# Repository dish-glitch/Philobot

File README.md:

# Philo — Autonomous Person-Following Robot

**A 4-wheeled ground robot that locks onto a person using real-time YOLOv8 pose detection and follows them across a room. Raise your hand and it stops. Lower it and it follows again.**

---

## Schematic Preview

---

## PCB Preview

---

## Chassis Preview

*Coming soon — Fusion 360 render in progress*

---

## What It Does

A Raspberry Pi 5 runs YOLOv8 pose estimation on a live camera feed, detects the nearest person in frame, and continuously streams direction and speed commands to an ESP32 over UART. The ESP32 runs closed-loop PID speed control on four DC motors via dual H-bridge drivers. Three ultrasonic sensors on the front of the chassis act as an independent safety layer — if an obstacle is detected under 25cm, the ESP32 overrides the Pi command and stops regardless of what the vision stack says.

**Gesture control:** YOLOv8 tracks 17 body keypoints per person. When either wrist keypoint rises above the shoulder keypoint in frame coordinates, the Pi switches to STOP mode and holds it for 5 consecutive frames before acting — this debounces the detection and prevents flickering. Lowering the hand for 5 consecutive frames resumes following. Stop gesture confirmed working in testing.

**Sign language recognition:** The camera detects ASL hand signs in real time using MediaPipe hand landmarks and a trained classifier. Recognized letters are sent over UART to the ESP32 and displayed live on the onboard OLED (bench-tested on the Arduino stand-in; the ESP32 `ASL` handler is implemented and awaiting PCB bring-up). Initial testing on Pi 5 shows strong results for most letters — broader testing across different hands, lighting, and environments is still in progress.

**Obstacle avoidance:** Three HC-SR04 ultrasonic sensors (front-left at -30 degrees, front-center, front-right at +30 degrees) feed into a priority layer in ESP32 firmware. The Pi handles direction. The ESP32 handles not hitting things. These are separate concerns and intentionally kept that way.

---

## How It Works

```
+--------------------------------------------------+
|              Raspberry Pi 5                      |
|                                                  |
|  Camera -> YOLOv8n-pose -> keypoint extraction   |
|               |                                  |
|      Person bounding box offset                  |
|      Wrist vs. shoulder Y position               |
|               |                                  |
|      State machine (FOLLOWING / WAITING)         |
|               |                                  |
|      Serial command -> UART TX                   |
+---------------+----------------------------------+
                |  115200 baud UART
                |  Format: CMD <left> <right> <flags>  (-255..255)
                v
+--------------------------------------------------+
|              ESP32-WROOM-32                      |
|                                                  |
|  UART RX -> parse command                        |
|               |                                  |
|  Ultrasonic check (priority override)            |
|               |                                  |
|  PID speed control per motor side                |
|  PWM via LEDC peripheral at 20kHz               |
|               |                                  |
|  TB6612FNG x2 -> 4 DC motors with encoders      |
+--------------------------------------------------+
```

**Latency budget (targets):**

| Stage | Target |
|---|---|
| Camera capture | ~5ms |
| YOLOv8n-pose inference (imgsz=320) | ~70ms |
| Serial transmission | ~1ms |
| ESP32 motor response | ~5ms |
| **Total loop** | **~80ms (~12 Hz)** |

12 Hz is sufficient for following a walking person. A running person would expose the lag — but that is not the use case.

**Why UART and not I2C or SPI:** UART is asynchronous and trivially debuggable with a serial monitor. I2C requires the ESP32 to act as master which complicates the Pi-side code. SPI is faster than needed. UART at 115200 baud moves our 20-byte command packets in under 2ms. It is the right tool for this interface.

**Why TB6612FNG and not L298N:** The L298N drops ~2V across its internal transistors at 1A, wasting power as heat and requiring a heatsink. The TB6612FNG is a MOSFET H-bridge — nearly zero voltage drop, no heatsink needed, physically smaller. It is the correct motor driver for battery-powered mobile robots.

**Why YOLOv8n-pose and not separate detection and pose models:** One model pass gives you person detection and 17 keypoints simultaneously. Running two models would double inference time and add synchronization complexity. The nano pose model is marginally slower than nano detect-only and eliminates the entire second pipeline.

---

## Hardware

> Prices are estimates. Amazon prices fluctuate — verify before ordering. Order DigiKey parts together to share one flat shipping fee (~$8).

| Component | Purpose | Qty | Est. Price | Where |
|---|---|---|---|---|
| ESP32-WROOM-32 | Main MCU | 1 | ~$5 | Amazon |
| TB6612FNG Dual H-Bridge (bare IC, SSOP-24) | Motor driver (2 motors each) | 2 | ~$2 ea | DigiKey |
| MPU-6050 IMU | Tilt detection, auto-stop on tip-over | 1 | ~$2 | Amazon |
| JGA25-370 Gear Motors w/ Encoders (6V 200RPM) | Drive wheels | 4 | ~$8 ea | AliExpress |
| 80mm Rubber Wheels | Traction | 4 | ~$3 ea | AliExpress |
| HC-SR04 Ultrasonic Sensors | Obstacle detection | 3 | ~$1 ea | Amazon |
| SSD1306 OLED 0.96" I2C | Eyes + ASL display on mast | 2 | ~$4 ea | Amazon |
| 2S LiPo 2200mAh | Main battery | 1 | ~$14 | Amazon / HobbyKing |
| 2S LiPo Balance Charger | Charging | 1 | ~$10 | Amazon |
| Raspberry Pi 5 (4GB) | Vision compute | 1 | on hand | From friend — with active cooler |
| Raspberry Pi Camera Module 3 | 12MP, autofocus | 1 | on hand | Attached, confirmed working |
| AMS1117-3.3 LDO | 3.3V rail for ESP32 logic | 1 | ~$1 | DigiKey |
| Pololu D24V50F5 Buck (5V 5A) | 5V rail for Raspberry Pi | 1 | ~$30 | [Pololu](https://www.pololu.com/product/2851) |
| Littelfuse RGEF700 Polyfuse 7A | Battery overcurrent protection | 1 | ~$2 | DigiKey |
| AOD4185 P-channel MOSFET | Reverse polarity protection | 1 | ~$1 | DigiKey |
| Status LED (any 5mm) | Boot/status indicator | 1 | ~$1 | Amazon |
| Tactile switches 6mm THT | Reset + Boot buttons | 2 | ~$1 | Amazon |
| SMD Resistors 0603 assortment | Pull-ups, current limiting | — | ~$9 | Amazon |
| SMD Capacitors 0603/0805 assortment | HF decoupling bypass caps | — | ~$10 | Amazon |
| Electrolytic caps (1000µF 16V + 2×470µF 16V + 100µF 16V) | Bulk decoupling — order separately, not in SMD assortment | — | ~$5 | DigiKey |
| XT30 Connector Pair | Battery connector | 1 | ~$2 | Amazon |
| 2.54mm Pin Headers | Sensor and UART connectors | — | ~$6 | Amazon |
| CP2102 USB-UART Programmer | Flash ESP32 firmware | 1 | ~$7 | Amazon |
| Custom PCB — JLCPCB (5 boards) | From Gerbers | 1 run | ~$25 | [JLCPCB](https://jlcpcb.com) |
| PETG-CF Filament | Chassis | — | $0 | On hand |
| M2.5 / M3 Standoffs + Screws | Mounting hardware | — | ~$8 | Amazon |
| **Total** | | | **~$215** | |

---

## Repository Structure

```
Philo/
├── hardware/
│   └── kicad/
│       ├── Philo.kicad_sch           # Schematic (ESP32, motors, power, sensors)
│       ├── Philo- main.kicad_pcb     # PCB layout — 116×116mm 2-layer, 4x M3 mounting holes
│       └── gerbers/                  # Production files ready for JLCPCB
│           ├── *.gtl / *.gbl         # Front / back copper
│           ├── *.gts / *.gbs         # Solder mask
│           ├── *.gto / *.gbo         # Silkscreen
│           ├── *.gm1                 # Board outline
│           └── *.drl                 # Drill files
├── firmware/
│   ├── esp32/
│   │   ├── platformio.ini            # PlatformIO config (espressif32 6.9.0)
│   │   └── src/
│   │       ├── main.cpp              # Entry point — 10 Hz sensor + Pi loop
│   │       ├── pins.h                # All GPIO assignments (verified from netlist)
│   │       ├── motors.h / .cpp       # TB6612FNG H-bridge control (PWM via LEDC)
│   │       ├── encoders.h / .cpp     # Interrupt-based wheel encoder counting
│   │       ├── ultrasonic.h / .cpp   # HC-SR04 distance (L / C / R)
│   │       ├── imu.h / .cpp          # MPU-6050 over I²C (accel + gyro)
│   │       ├── display.h / .cpp      # SSD1306 OLED status display
│   │       └── pi_comm.h / .cpp      # UART text protocol to Raspberry Pi
│   ├── arduino/                      # Uno bench-test sketches (ESP32 stand-in)
│   └── pico/                         # Pico MicroPython bench tests (experimental)
├── mechanical/
│   ├── Philo- main.step              # 3D board export
│   ├── fusion360/                    # Chassis CAD source files
│   └── stl/                         # Print-ready STL files
├── vision/
│   └── rpi/                         # YOLOv8 + gesture + ASL + Xbox manual drive (Python)
└── docs/
    ├── images/                       # Photos, renders, wiring diagrams
    ├── PRE_BUILD_LOCK.md             # Design freeze checklist
    └── RESEARCH.md                   # Reference robots, papers, and datasheets used
```

---

## Build Log

| Date | Milestone |
|---|---|
| June 16, 2026 | Project started. Repository initialized. Team of 4 assembled. |
| June 17, 2026 | KiCad schematic started — ESP32, motor drivers, power block |
| June 21, 2026 | PCB schematic complete, ERC clean |
| June 21, 2026 | PCB layout complete, DRC clean, Gerbers exported |
| June 22, 2026 | ESP32 firmware skeleton complete — all modules compile (motors, encoders, ultrasonic, IMU, OLED, Pi UART) |
| June 22, 2026 | Gesture stop function confirmed working (tested on Arduino) |
| June 22, 2026 | Sign language recognition working for subset of letters — OLED display output confirmed |
| June 22, 2026 | Chassis design started in Fusion 360 |
| June 28, 2026 | Upgraded to Raspberry Pi 5 with active cooler — camera confirmed working |
| June 28, 2026 | YOLOv8n-pose running live on Pi 5 — person following confirmed |
| June 28, 2026 | ASL sign recognition working well for most letters in initial testing — broader validation ongoing |
| — | PCB ordered from JLCPCB |
| — | Chassis v1 printed in PETG-CF |
| — | PCB arrived, soldered, power-on test passed |
| — | Basic motor spin confirmed over serial |
| — | First person following on robot hardware |
| — | Gesture control working on robot |
| — | Obstacle avoidance tuned |
| — | Demo video filmed |
| Aug 17, 2026 | School starts — project complete |

---

## Status

- [x] KiCad schematic — complete, ERC clean
- [x] PCB layout — complete, DRC clean, Gerbers exported
- [x] ESP32 firmware skeleton — all modules compile (motors, encoders, ultrasonic, IMU, OLED, Pi UART)
- [x] ESP32 safety layer — 500ms watchdog, obstacle override, tilt cutoff, sequential ultrasonic firing (needs hardware validation)
- [x] Pi vision stack — YOLOv8 person following + gesture + ASL running on Pi 5
- [x] YOLOv8n-pose live on Pi 5 — person following confirmed working
- [x] Gesture stop — confirmed working in bench testing
- [x] ASL sign recognition — working well for most letters in initial testing; broader testing ongoing
- [ ] Gesture sensitivity tuning — currently too sensitive, fix tracked in issue #2
- [ ] PCB fabrication (JLCPCB)
- [ ] Chassis design (Fusion 360) — in progress
- [ ] Chassis printed
- [ ] PID speed loop (ESP32)
- [ ] Ultrasonic obstacle avoidance tuning
- [ ] Full system integration on robot hardware
- [ ] Demo video

---

## Team

| Person | Role |
|---|---|
| [@dish-glitch](https://github.com/dish-glitch) | PCB design (KiCad) + ESP32 firmware |
| [@sivathamizhan](https://github.com/sivathamizhan) & [@dish-glitch](https://github.com/dish-glitch) | Raspberry Pi vision stack — YOLOv8, gesture detection, serial comms |
| [@hummos430](https://github.com/hummos430) | Chassis design in Fusion 360 + 3D printing in PETG-CF |
| [@dish-glitch](https://github.com/dish-glitch), [@hummos430](https://github.com/hummos430), [@sivathamizhan](https://github.com/sivathamizhan) | Mechanical assembly + integration testing |

---

## AI Tools Used

We used Claude (Anthropic) as a reference tool during this project and are disclosing it openly. We had no robotics program, no teacher, and no mentor. AI filled the role a textbook or more experienced teammate would have filled if we'd had access to one.

**Where Claude helped:**

- Reviewing GPIO assignments from the KiCad netlist and catching wiring errors before we soldered anything
- Drafting initial ESP32 firmware modules as a starting point — the team then read through, modified, tested, and debugged everything on actual hardware
- Diagnosing a PlatformIO build failure (`pins_arduino.h` not found) caused by a version conflict between espressif32@6.9.0 and 7.0.1
- Explaining why specific hardware choices make sense (TB6612FNG vs L298N, YOLOv8n-pose vs separate models, UART vs I2C) so we could make informed decisions
- Helping structure the GitHub repository and draft documentation to a presentable structure. 
- Providing weight and dimension constraints for the chassis — specifically, what size the enclosure needs to be so the motors can actually move it. The chassis itself is fully designed by the team in Fusion 360

**What the team built and owns:**

- All hardware decisions — component selection, schematic design, and PCB layout in KiCad
- The full vision stack — YOLOv8 inference pipeline, ASL classifier, gesture detection, serial comms — written and tested by the team
- All physical testing and iteration — every debug session, hardware fix, and tuning pass was done by us in the real world
- The chassis design in Fusion 360 — built by our mechanical lead from scratch
- Every journal entry — written by the team in our own words

We are happy to answer questions about any part of this project. We have used AI to help build it, but we understand everything we built. If AI helped create any line of code or suggested a part that seemed better, we did the research to understand what that part or code does and why — before it went into the project. The reference robots, papers, and datasheets we used to back up those decisions are collected in [`docs/RESEARCH.md`](docs/RESEARCH.md).

---

## License

MIT — use, modify, share freely. See [LICENSE](LICENSE).

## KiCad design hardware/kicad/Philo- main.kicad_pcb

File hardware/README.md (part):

# Hardware — Philo PCB

**Owner: [@dish-glitch](https://github.com/dish-glitch)**

---

## Overview
The PCB was designed as the main interface for philo, it distributes the power and connects the raspberry Pi and ESP32. It drives the motors, and provides connectors for the sensors used throughout the robot. 

**Current phase: PCB fabrication.** Schematic complete (0 ERC errors), PCB layout complete (DRC clean, Gerbers exported). Kicad files: [`hardware/kicad/`](kicad/).

**For the actual build, start here:**
- **[BOM.md](BOM.md)** — complete parts list 
- **[SCHEMATIC.md](SCHEMATIC.md)** — completed, for reference

---

## Component Specifications (Verified from Datasheets)

The components below are the parts selected for the current revision of the PCB. Main componets are here incase of debugging. 

| Component | Key Specs | Source | Weight |
|---|---|---|---|
| ESP32-WROOM-32 | 240MHz dual-core, 520KB SRAM, 3.3V, 18x25.5x3.1mm | [Espressif datasheet](https://www.espressif.com/sites/default/files/documentation/esp32-wroom-32d_esp32-wroom-32u_datasheet_en.pdf) | 2.5g |
| TB6612FNG x2 | 1.2A continuous / 3.2A peak per channel, 4.5-13.5V motor, 2.7-5.5V logic, 100kHz PWM max | [Toshiba datasheet](https://cdn-shop.adafruit.com/datasheets/TB6612FNG_datasheet_en_20121101.pdf) | 1.5g each |
| MPU-6050 (GY-521 module) | 3-axis accel +/-16g, 3-axis gyro +/-2000 deg/s, I2C, 3.3-5V, 21x15mm | [InvenSense datasheet](https://product.tdk.com/en/search/sensor/mortion-inertial/imu/info?part_no=MPU-6050) | 13g |
| HC-SR04 x3 | 5V, <15mA, 2-400cm range, 40kHz, 45x20x15mm | [Sparkfun datasheet](https://cdn.sparkfun.com/datasheets/Sensors/Proximity/HCSR04.pdf) | 10g each |
| AMS1117-3.3 LDO | 3.3V out, 800mA max, SOT-223 package | AMS datasheet | <1g |
| Pololu D24V50F5 Buck (5V/5A) | 4.5-38V in, 5.0V fixed out, 5A continuous near capacity with Pi 5 (up to 4.5A peak) | [Pololu D24V50F5](https://www.pololu.com/product/2851) | ~5g |
| JGA25-370 x4 | 6V, 200 RPM, 1.8-2.2 kg*cm stall torque, 4mm D-shaft, 25mm body diameter | Product page | 90g each |
| 2S LiPo 2200mAh | 7.4V nominal, 8.4V full, 6.4V cutoff, 97-130g depending on model | Gens Ace product page | ~110g |
| XT30 Connector | 30A continuous, gold plated, compact | XT30 spec | 3g per pair |

---

## PCB Block Architecture

### Block 1 — Microcontroller: ESP32-WROOM-32

the ESP32 is responsible for the robot's real time control. it hands the motor control, reads the ultrasonic sensors and IMU. it also communicates with the PI over UART and updates the oled screens. 

**Decoupling:** we placed one 100nF ceramic cap and one 10uF electrolytic cap between VCC and GND, as close to the module as possible. These capacotors help keep the esp32 stable during current changes. 

**Brownout detection:** we enabled the ESP32 hardware brownout detector in firmware and set brownout threshold to 2.7V via esp_reset_reason and brownout config. This allows the esp32 to reset cleanly rather than staying in an undefined state. 

**Programming:** 6-pin header (TX, RX, EN, GPIO0, 3.3V, GND). CP2102 plugs in here!

Boot button: tactile button from GPIO0 to GND needed for entering flash mode. 

### Block 2 — Motor Drivers: TB6612FNG x2 

Two TB6612FNG ICs. Each drives two motors. Total: 4 motors driven.

**Why we chose the TB6612FNG:** Early in the project we were going to pick the L298N becuase its common and used in many starting projects, but after looking at the voltage drop and power loss we decided to use the TB6612FNG. Because it uses MOSFET instead of bipolar transistors it wastes less power while aslo delivering more of the battery voltage to the motors.  

**Wiring each TB6612FNG:**
- PWMA, AIN1, AIN2 from ESP32 GPIO
- AO1, AO2 to motor A terminals
- PWMB, BIN1, BIN2, BO1, BO2 for motor B
- STBY tied HIGH (3.3V) permanently — LOW disables all outputs
- VM to VBAT (motor voltage, up to 13.5V)
- VCC to 3.3V logic

**TB6612FNG thermal note with JGA25-370 motors:** The JGA25-370 at 7.4V running at 40% load draws ~0.5A per motor. However, at brief stall (before the firmware watchdog triggers at 500ms), stall current at 7.4V can reach 1.5-2.2A per motor, exceeding the 1.2A continuous rating but within the 3.2A peak. The IC handles this for brief moments. Ensure the TB6612FNG KiCad footprint has its exposed thermal pad connected to a GND copper pour on the PCB. This provides a thermal path from the die to the board. If either IC is hot to the touch after Test 2 (repeated reversals), increase the copper pour area under the chip.

**Back-EMF on motor reversal:** we also found that the when motor is commanded to reverse direction mid-spin, it briefly acts as a generator. This creates a voltage spike back into the VM pin. The TB6612FNG has internal flyback diodes on all output transistors that clamp this spike to VM. The 470uF bulk cap at each TB6612FNG VM pin (see Section: Ground Architecture and Decoupling) further absorbs these transients.

**Placement:** Both TB6612FNG ICs on the same side as motor output connectors. Motor output traces (AO1, AO2, BO1, BO2) minimum 1.2mm. Short and direct to connectors.

### Block 3 — Power Architecture

The main power system. This is one of the most important parts of the PCB due to its important purpose of reliablly supplying power to the raspberry pi, esp32, motors, and the sensors.  

**Input: 2S LiPo via XT30**

Voltage range: 6.4V (discharged) to 8.4V (fully charged). 7A-rated polyfuse on input line (e.g., Littelfuse RGEF700) — trips at sustained overcurrent, resets after cooldown. P-channel MOSFET for reverse polarity protection.

**Why 7A, not 5A:** A polyfuse has nonzero resistance that increases as it heats up. A 5A-rated polyfuse at 3A normal load runs warm and its resistance rises to 0.1-0.5 ohm, causing 0.3-1.5V sag on VBAT before it ever trips. A 7A-rated part runs cold at our 3A normal current (resistance stays in milliohm range), so there is no sag during operation. Protection still works — fault currents above 7A trip it cleanly.

**3.3V Rail: AMS1117-3.3 LDO**

Powers: ESP32, MPU-6050, TB6612FNG logic, sensor pull-ups, LEDs.

**Input: 5V rail (from D24V50F5 output) — NOT from VBAT directly.**

Reason: At 8.4V VBAT input, the AMS1117 dissipates (8.4 - 3.3) x 0.27A = 1.38W. In SOT-223, that is a junction temperature of ~135C at 25C ambient, which is at or above the 125C maximum rating. Fed from 5V instead, dissipation is (5.0 - 3.3) x 0.27A = 0.46W, estimated junction temperature ~62C. Safe.

One reviewer concern was that cascading from 5V "couples Pi rail noise into ESP32 rail." This is overstated: the AMS1117 is a linear regulator with ~65dB PSRR at low frequencies, meaning 5V ripple is attenuated 1800x at the 3.3V output. If the 5V rail sags badly enough to matter for ESP32, the Pi is already browned out — that is a separate problem addressed by the 1000uF cap.

Caps: 10uF electrolytic + 100nF ceramic on both input and output pins. Required for AMS1117 stability — without them the output oscillates at high frequency.

Max load: ~270mA. Rated 800mA. Adequate headroom.

**5V Rail: Pololu D24V50F5 Buck Converter (5V, 5A)**

> Revision history: MP2307 (1.2A) was the original part — far too small, would have burned out. Then MP1584EN (3A) — adequate but tight: Pi at 2.5-3.0A + AMS1117 cascade 0.27A = ~2.77A on a 3A part, marginal once derated for an enclosed chassis. Final part is the **D24V50F5 (5A)** for real headroom on the most demo-critical rail. Pi brownout is the #1 demo-killer, so this rail gets margin.

Input: VBAT (6.4-8.4V)
Output: 5.0V (fixed — no trimpot to set, unlike the MP1584EN module)
EN pin: tie to VIN or leave floating (internal pull-up enables by default). PG (power-good) pin optional.

**Total 5V load: Pi 3.5A typical (4.5A peak) + AMS1117 cascade 0.27A = ~3.77A typical.** D24V50F5 rated 5A. At peak Pi load the margin is only ~0.5A — monitor for throttling during full inference. Active cooler on the Pi 5 mitigates thermal throttling and reduces average power draw.

**Output capacitors — updated from earlier revision:**
- 1000uF electrolytic (upgraded from 100uF based on Pi inrush spike analysis)
- 100nF ceramic in parallel

Why 1000uF: When the Pi 5 CPU ramps from idle to full inference load, it draws a current spike faster than the converter's control loop can respond (~microseconds). The 1000uF cap supplies that spike locally while the converter catches up. At a 3A spike for 1ms, 1000uF holds the voltage within 3mV of setpoint. 100uF would sag by 30mV — enough to trigger the Pi's undervoltage warning. Keep this cap even with the 5A buck 

5V connects to Pi via 2-pin header to GPIO pin 2 (5V) and pin 6 (GND). 

**Power sequencing note:** ESP32 boots in ~300ms. Pi takes 20-30 seconds. Firmware default state: all motors stopped, watchdog running. Motors do not move until first valid CMD packet received from Pi.

### Block 4 — Ground Architecture and Decoupling

While reviewing the power system, I realized the PCB layout mattered just as much as the schematic. Most of the components were already connected correctly, but poor grounding can still cause random resets and communication issues

**The problem:** Motor switching at 20kHz creates high-frequency current spikes through the ground path. If motor return current and ESP32 ground share any trace segment, the voltage difference across that trace's resistance injects noise into the ESP32's ground reference. This causes:
- Ghost resets when motors start or reverse
- UART data corruption on sharp direction changes
- Ultrasonic echo timing errors during motor switching
- IMU readings spiking during acceleration

**The fix — ground plane:**

Use the bottom copper layer as a solid ground plane. In KiCad: copper fill on back copper layer, set to GND net, pour.

This gives all ground connections (motor return, ESP32 GND, sensor GND, LDO GND) a low-impedance path back to the battery negative terminal.

**Single star point:** The battery negative (GND from XT30) should be the first ground connection on the board. Everything else connects to the plane, which connects to this point. 

**Bulk capacitors at each TB6612FNG:**

we have one 470uF electrolytic capacitor directly at each TB6612FNG VM pin (motor supply voltage). These absorb the current spike when a motor starts from rest or reverses direction. Without them, the spike travels back to the battery and couples into the 3.3V and 5V rails through shared impedance.

Component count: 2x 470uF (one per TB6612FNG IC), placed within 3mm of the VM pin.

**Decoupling cap placement rules:**
- 100nF ceramic caps: within 2mm of every IC power pin
- 470uF motor bulk caps: within 3mm of TB6612FNG VM pins
- 1000uF Pi rail cap: within 5mm of D24V50F5 output
- All caps connect to ground plane via short vias, not via trace segments

### Block 5 — IMU: MPU-6050

Connects via I2C (SDA/SCL). Default address 0x68. Document I2C address map.

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
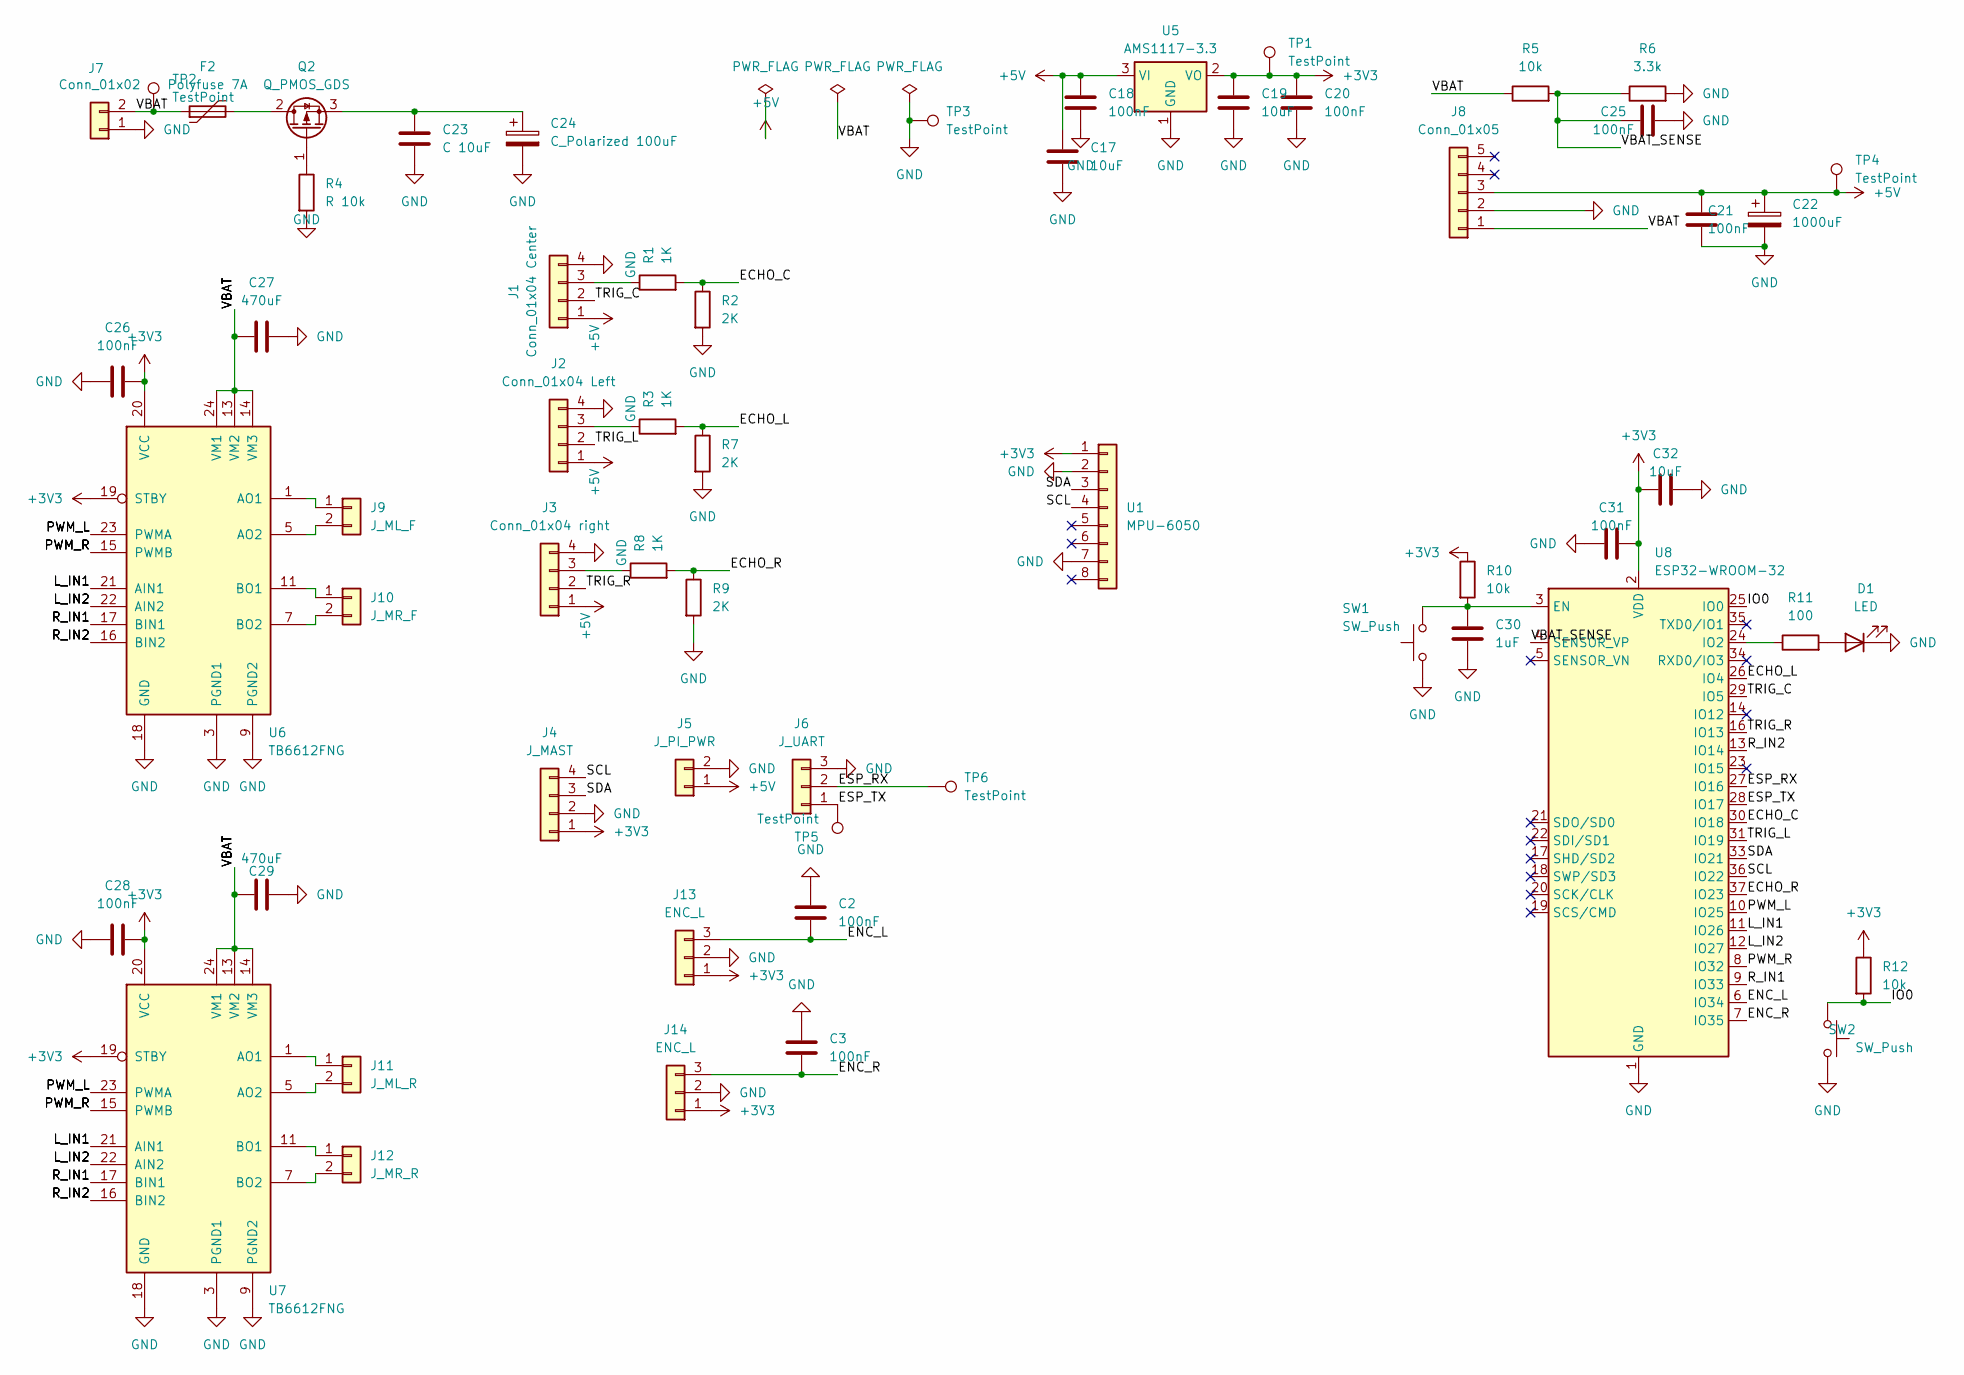
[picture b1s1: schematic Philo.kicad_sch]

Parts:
C2, C3, C18, C20, C21, C25, C26, C28, C31: 100nF; C_0603_1608Metric
C17, C19, C32: 10uF; C_0805_2012Metric
C22: 1000uF; CP_Radial_D12.5mm_P5.00mm
C23: C 10uF; C_0805_2012Metric
C24: C_Polarized 100uF; CP_Radial_D6.3mm_P2.50mm
C27, C29: 470uF; CP_Radial_D10.0mm_P5.00mm
C30: 1uF; C_0603_1608Metric
D1: LED; LED_0805_2012Metric
F2: Polyfuse 7A; CP_Radial_D10.0mm_P5.00mm
J1: Conn_01x04 Center; PinHeader_1x04_P2.54mm_Vertical
J2: Conn_01x04 Left; PinHeader_1x04_P2.54mm_Vertical
J3: Conn_01x04 right; PinHeader_1x04_P2.54mm_Vertical
J4: J_MAST; PinHeader_1x04_P2.54mm_Vertical
J5: J_PI_PWR; PinHeader_1x02_P2.54mm_Vertical
J6: J_UART; PinHeader_1x03_P2.54mm_Vertical
J7: Conn_01x02; PinHeader_1x02_P2.54mm_Vertical
J8: Conn_01x05; PinHeader_1x05_P2.54mm_Vertical
J9: J_ML_F; PinHeader_1x02_P2.54mm_Vertical
J10: J_MR_F; PinHeader_1x02_P2.54mm_Vertical
J11: J_ML_R; PinHeader_1x02_P2.54mm_Vertical
J12: J_MR_R; PinHeader_1x02_P2.54mm_Vertical
J13, J14: ENC_L; PinHeader_1x03_P2.54mm_Vertical
Q2: Q_PMOS_GDS; TO-252-3_TabPin2
R1, R3, R8: 1K; R_0603_1608Metric
R2, R7, R9: 2K; R_0603_1608Metric
R4: R 10k; R_0603_1608Metric
R5, R10, R12: 10k; R_0603_1608Metric
R6: 3.3k; R_0603_1608Metric
R11: 100; R_0603_1608Metric
SW1, SW2: SW_Push; SW_PUSH_6mm
TP1, TP2, TP3, TP4, TP5, TP6: TestPoint; TestPoint_Pad_D1.5mm
U1: MPU-6050
U5: AMS1117-3.3; SOT-223-3_TabPin2
U6, U7: TB6612FNG; SSOP-24_5.3x8.2mm_P0.65mm
U8: ESP32-WROOM-32

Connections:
+3V3: C19.1, C20.1, C26.2, C28.2, C31.1, C32.1, J4.1, J13.1, J14.1, R10.1, R12.1, TP1.1, U1.1, U1.8 (VLOGIC), U5.2 (VO), U6.19 (STBY), U6.20 (VCC), U7.19 (STBY), U7.20 (VCC), U8.2 (VDD); also elsewhere on the board
+5V: C17.1, C18.1, C21.1, C22.1, J1.1, J2.1, J3.1, J5.1, J8.3, TP4.1, U5.3 (VI)
/Combined/ECHO_C: R1.2, R2.1, U8.30 (IO18)
/Combined/ECHO_L: R3.2, R7.1, U8.26 (IO4)
/Combined/ECHO_R: R8.2, R9.1, U8.37 (IO23)
/Combined/ENC_L: C2.2, J13.3, U8.6 (IO34)
/Combined/ENC_R: C3.2, J14.3, U8.7 (IO35)
/Combined/ESP_RX: J6.2, TP6.1, U8.27 (IO16)
/Combined/ESP_TX: J6.1, TP5.1, U8.28 (IO17)
/Combined/IO0: R12.2, SW2.1, U8.25 (IO0)
/Combined/L_IN1: U6.21 (AIN1), U7.21 (AIN1), U8.11 (IO26)
/Combined/L_IN2: U6.22 (AIN2), U7.22 (AIN2), U8.12 (IO27)
/Combined/PWM_L: U6.23 (PWMA), U7.23 (PWMA), U8.10 (IO25)
/Combined/PWM_R: U6.15 (PWMB), U7.15 (PWMB), U8.8 (IO32)
/Combined/R_IN1: U6.17 (BIN1), U7.17 (BIN1), U8.9 (IO33)
/Combined/R_IN2: U6.16 (BIN2), U7.16 (BIN2), U8.13 (IO14)
/Combined/SCL: J4.4, U1.4, U8.36 (IO22); also elsewhere on the board
/Combined/SDA: J4.3, U1.3, U8.33 (IO21); also elsewhere on the board
/Combined/TRIG_C: J1.2, U8.29 (IO5)
/Combined/TRIG_L: J2.2, U8.31 (IO19)
/Combined/TRIG_R: J3.2, U8.16 (IO13)
/Combined/VBAT: C27.1, C29.1, F2.1, J7.2, J8.1, R5.1, TP2.1, U6.13 (VM2), U6.14 (VM3), U6.24 (VM1), U7.13 (VM2), U7.14 (VM3), U7.24 (VM1)
/Combined/VBAT_SENSE: C25.1, R5.2, R6.1, U8.4 (SENSOR_VP)
GND: C2.1, C3.1, C17.2, C18.2, C19.2, C20.2, C21.2, C22.2, C23.2, C24.2, C25.2, C26.1, C27.2, C28.1, C29.2, C30.2, C31.2, C32.2, D1.1 (K), J1.4, J2.4, J3.4, J4.2, J5.2, J6.3, J7.1, J8.2, J13.2, J14.2, R2.2, R4.2, R6.2, R7.2, R9.2, SW1.1, SW2.2, TP3.1, U1.2, U1.7, U5.1 (GND), U6.3 (PGND1), U6.4 (PGND1), U6.9 (PGND2), U6.10 (PGND2), U6.18 (GND), U7.3 (PGND1), U7.4 (PGND1), U7.9 (PGND2), U7.10 (PGND2), U7.18 (GND), U8.1 (GND), U8.15 (GND), U8.38 (GND), U8.39 (GND); also elsewhere on the board
unnamed: D1.2 (A), R11.2
unnamed: J1.3, R1.1
unnamed: J2.3, R3.1
unnamed: J3.3, R8.1
unnamed: J9.1, U6.1 (AO1), U6.2 (AO1)
unnamed: J9.2, U6.5 (AO2), U6.6 (AO2)
unnamed: J10.1, U6.11 (BO1), U6.12 (BO1)
unnamed: J10.2, U6.7 (BO2), U6.8 (BO2)
unnamed: J11.1, U7.1 (AO1), U7.2 (AO1)
unnamed: J11.2, U7.5 (AO2), U7.6 (AO2)
unnamed: J12.1, U7.11 (BO1), U7.12 (BO1)
unnamed: J12.2, U7.7 (BO2), U7.8 (BO2)
unnamed: F2.2, Q2.2 (D)
unnamed: Q2.1 (G), R4.1
unnamed: C23.1, C24.1, Q2.3 (S)
unnamed: C30.1, R10.2, SW1.2, U8.3 (EN)
unnamed: R11.1, U8.24 (IO2)

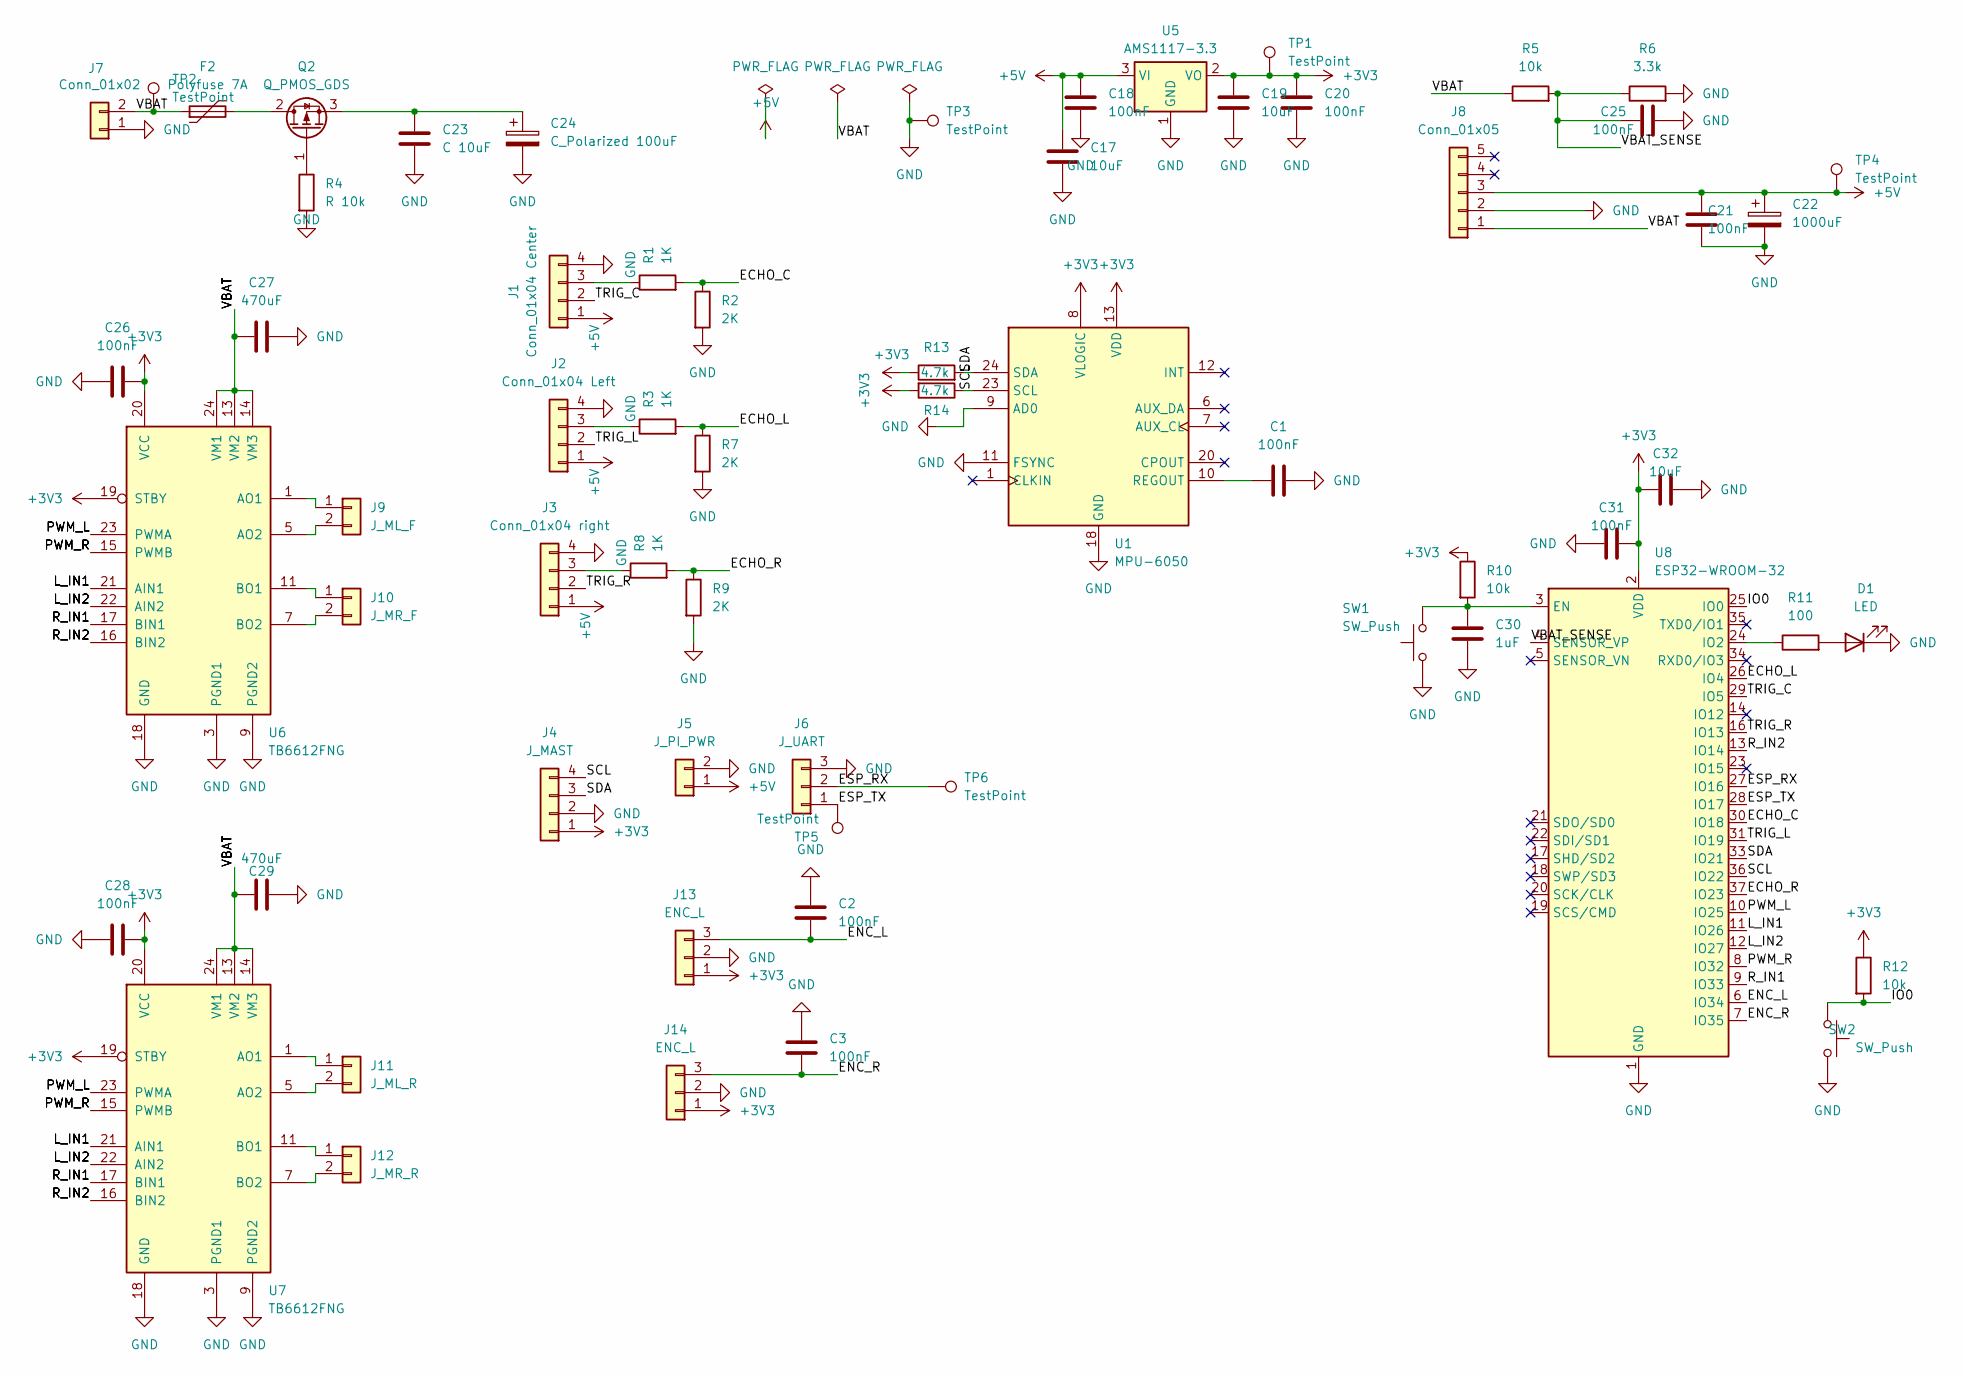
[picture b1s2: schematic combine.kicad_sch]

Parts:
C1, C2, C3, C18, C20, C21, C25, C26, C28, C31: 100nF; C_0603_1608Metric
C17, C19, C32: 10uF; C_0805_2012Metric
C22: 1000uF; CP_Radial_D12.5mm_P5.00mm
C23: C 10uF; C_0805_2012Metric
C24: C_Polarized 100uF; CP_Radial_D6.3mm_P2.50mm
C27, C29: 470uF; CP_Radial_D10.0mm_P5.00mm
C30: 1uF; C_0603_1608Metric
D1: LED; LED_0805_2012Metric
F2: Polyfuse 7A; CP_Radial_D10.0mm_P5.00mm
J1: Conn_01x04 Center; PinHeader_1x04_P2.54mm_Vertical
J2: Conn_01x04 Left; PinHeader_1x04_P2.54mm_Vertical
J3: Conn_01x04 right; PinHeader_1x04_P2.54mm_Vertical
J4: J_MAST; PinHeader_1x04_P2.54mm_Vertical
J5: J_PI_PWR; PinHeader_1x02_P2.54mm_Vertical
J6: J_UART; PinHeader_1x03_P2.54mm_Vertical
J7: Conn_01x02; PinHeader_1x02_P2.54mm_Vertical
J8: Conn_01x05; PinHeader_1x05_P2.54mm_Vertical
J9: J_ML_F; PinHeader_1x02_P2.54mm_Vertical
J10: J_MR_F; PinHeader_1x02_P2.54mm_Vertical
J11: J_ML_R; PinHeader_1x02_P2.54mm_Vertical
J12: J_MR_R; PinHeader_1x02_P2.54mm_Vertical
J13, J14: ENC_L; PinHeader_1x03_P2.54mm_Vertical
Q2: Q_PMOS_GDS; TO-252-3_TabPin2
R1, R3, R8: 1K; R_0603_1608Metric
R2, R7, R9: 2K; R_0603_1608Metric
R4: R 10k; R_0603_1608Metric
R5, R10, R12: 10k; R_0603_1608Metric
R6: 3.3k; R_0603_1608Metric
R11: 100; R_0603_1608Metric
R13, R14: 4.7k; R_0603_1608Metric
SW1, SW2: SW_Push; SW_PUSH_6mm
TP1, TP2, TP3, TP4, TP5, TP6: TestPoint; TestPoint_Pad_D1.5mm
U1: MPU-6050; PinHeader_1x08_P2.54mm_Vertical
U5: AMS1117-3.3; SOT-223-3_TabPin2
U6, U7: TB6612FNG; SSOP-24_5.3x8.2mm_P0.65mm
U8: ESP32-WROOM-32

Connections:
+3V3: C19.1, C20.1, C26.2, C28.2, C31.1, C32.1, J4.1, J13.1, J14.1, R10.1, R12.1, R13.1, R14.2, TP1.1, U1.1, U1.8 (VLOGIC), U1.13 (VDD), U5.2 (VO), U6.19 (STBY), U6.20 (VCC), U7.19 (STBY), U7.20 (VCC), U8.2 (VDD)
+5V: C17.1, C18.1, C21.1, C22.1, J1.1, J2.1, J3.1, J5.1, J8.3, TP4.1, U5.3 (VI)
/Combined/ECHO_C: R1.2, R2.1, U8.30 (IO18)
/Combined/ECHO_L: R3.2, R7.1, U8.26 (IO4)
/Combined/ECHO_R: R8.2, R9.1, U8.37 (IO23)
/Combined/ENC_L: C2.2, J13.3, U8.6 (IO34)
/Combined/ENC_R: C3.2, J14.3, U8.7 (IO35)
/Combined/ESP_RX: J6.2, TP6.1, U8.27 (IO16)
/Combined/ESP_TX: J6.1, TP5.1, U8.28 (IO17)
/Combined/IO0: R12.2, SW2.1, U8.25 (IO0)
/Combined/L_IN1: U6.21 (AIN1), U7.21 (AIN1), U8.11 (IO26)
/Combined/L_IN2: U6.22 (AIN2), U7.22 (AIN2), U8.12 (IO27)
/Combined/PWM_L: U6.23 (PWMA), U7.23 (PWMA), U8.10 (IO25)
/Combined/PWM_R: U6.15 (PWMB), U7.15 (PWMB), U8.8 (IO32)
/Combined/R_IN1: U6.17 (BIN1), U7.17 (BIN1), U8.9 (IO33)
/Combined/R_IN2: U6.16 (BIN2), U7.16 (BIN2), U8.13 (IO14)
/Combined/SCL: J4.4, R14.1, U1.4, U1.23 (SCL), U8.36 (IO22)
/Combined/SDA: J4.3, R13.2, U1.3, U1.24 (SDA), U8.33 (IO21)
/Combined/TRIG_C: J1.2, U8.29 (IO5)
/Combined/TRIG_L: J2.2, U8.31 (IO19)
/Combined/TRIG_R: J3.2, U8.16 (IO13)
/Combined/VBAT: C27.1, C29.1, F2.1, J7.2, J8.1, R5.1, TP2.1, U6.13 (VM2), U6.14 (VM3), U6.24 (VM1), U7.13 (VM2), U7.14 (VM3), U7.24 (VM1)
/Combined/VBAT_SENSE: C25.1, R5.2, R6.1, U8.4 (SENSOR_VP)
GND: C1.1, C2.1, C3.1, C17.2, C18.2, C19.2, C20.2, C21.2, C22.2, C23.2, C24.2, C25.2, C26.1, C27.2, C28.1, C29.2, C30.2, C31.2, C32.2, D1.1 (K), J1.4, J2.4, J3.4, J4.2, J5.2, J6.3, J7.1, J8.2, J13.2, J14.2, R2.2, R4.2, R6.2, R7.2, R9.2, SW1.1, SW2.2, TP3.1, U1.2, U1.7, U1.9 (AD0), U1.11 (FSYNC), U1.18 (GND), U5.1 (GND), U6.3 (PGND1), U6.4 (PGND1), U6.9 (PGND2), U6.10 (PGND2), U6.18 (GND), U7.3 (PGND1), U7.4 (PGND1), U7.9 (PGND2), U7.10 (PGND2), U7.18 (GND), U8.1 (GND), U8.15 (GND), U8.38 (GND), U8.39 (GND)
unnamed: C1.2, U1.10 (REGOUT)
unnamed: D1.2 (A), R11.2
unnamed: J1.3, R1.1
unnamed: J2.3, R3.1
unnamed: J3.3, R8.1
unnamed: J9.1, U6.1 (AO1), U6.2 (AO1)
unnamed: J9.2, U6.5 (AO2), U6.6 (AO2)
unnamed: J10.1, U6.11 (BO1), U6.12 (BO1)
unnamed: J10.2, U6.7 (BO2), U6.8 (BO2)
unnamed: J11.1, U7.1 (AO1), U7.2 (AO1)
unnamed: J11.2, U7.5 (AO2), U7.6 (AO2)
unnamed: J12.1, U7.11 (BO1), U7.12 (BO1)
unnamed: J12.2, U7.7 (BO2), U7.8 (BO2)
unnamed: F2.2, Q2.2 (D)
unnamed: Q2.1 (G), R4.1
unnamed: C23.1, C24.1, Q2.3 (S)
unnamed: C30.1, R10.2, SW1.2, U8.3 (EN)
unnamed: R11.1, U8.24 (IO2)

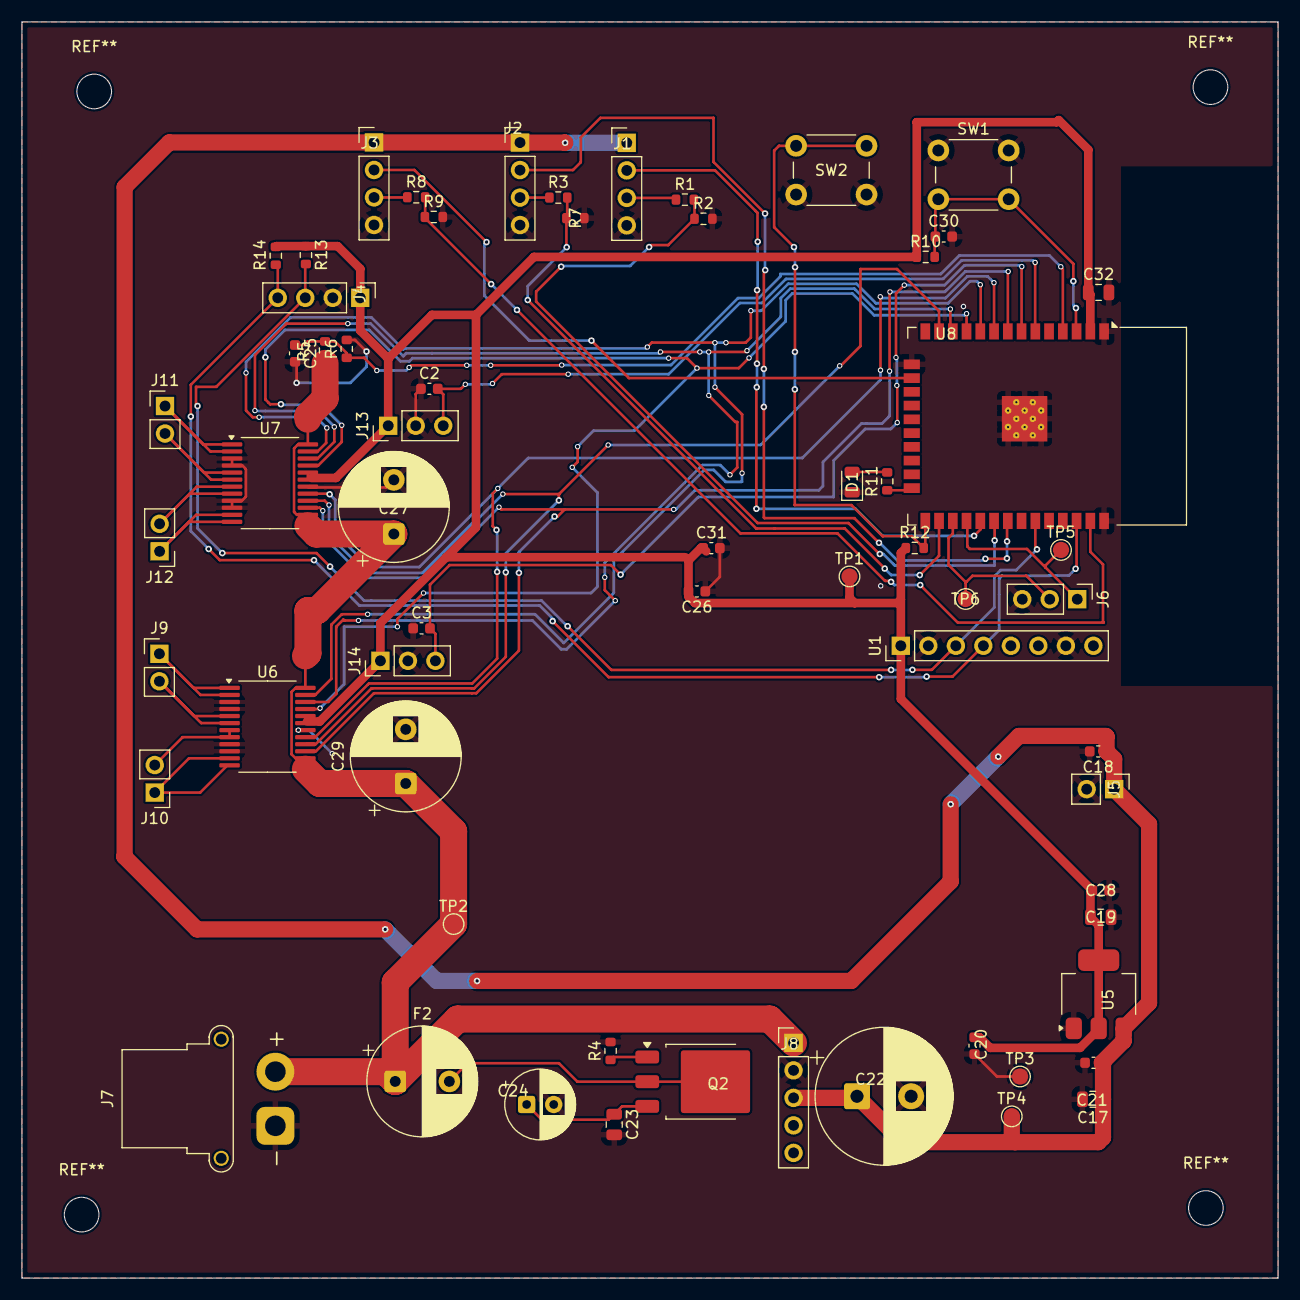
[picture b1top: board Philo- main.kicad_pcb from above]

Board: 2 copper layers, 116.0 x 116.0 mm, 62 parts (0 on the bottom side), 41 nets.

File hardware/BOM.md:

# Philo — Bill of Materials (Complete)

**Status: Schematic complete, ERC clean, PCB layout complete, DRC clean, Gerbers exported. Ready to order.**

This is the authoritative parts list matching the annotated KiCad schematic. Reference designators reflect post-annotation numbering.

---

## Active Components

| Ref | Part | Value / Spec | Footprint | Qty | Notes |
|---|---|---|---|---|---|
| U8 | ESP32-WROOM-32 | 240MHz, 4MB flash | RF_Module:ESP32-WROOM-32 | 1 | Castellated SMD module |
| J8 | Pololu D24V50F5 | 5.0V fixed out, 5A buck | PinHeader_1x05_P2.54mm | 1 | Complete module — no external inductor/feedback needed. VIN←VBAT, VOUT→+5V |
| U5 | AMS1117-3.3 | 3.3V LDO, 800mA | SOT-223-3_TabPin2 | 1 | Input from **+5V rail**, NOT VBAT — thermal lock decision |
| U6 | TB6612FNG | Dual H-bridge, 1.2A/ch | SSOP-24_5.3x8.2mm_P0.65mm | 1 | Left-front + right-front motors |
| U7 | TB6612FNG | Dual H-bridge, 1.2A/ch | SSOP-24_5.3x8.2mm_P0.65mm | 1 | Left-rear + right-rear motors |
| U1 | MPU-6050 (GY-521 module) | 6-axis IMU, I2C | PinHeader_1x08_P2.54mm | 1 | Address 0x68 (AD0→GND). Use GY-521 breakout |
| Q2 | AOD4185 P-channel MOSFET | Vds>30V, 10A | TO-252-3_TabPin2 | 1 | Reverse-polarity protection. Drain=battery side, Source=VBAT rail |
| D1 | Status LED | Any color | LED_0805_2012Metric | 1 | GPIO2 → R11 (100Ω) → LED → GND |

---

## Off-Board Modules (connect via headers)

| Part | Spec | Qty | Connector | Est. Price | Notes |
|---|---|---|---|---|---|
| OLED display | SSD1306, 128x64, I2C, 0.96 inch | 2 | J4 (J_MAST) | ~$4 ea (Amazon) | One at 0x3C (telemetry / left eye), one at 0x3D (right eye). Set address via solder jumper on back of module. Mounted on camera mast as eyes. **Buy 2.** |
| HC-SR04 | Ultrasonic, 5V | 3 | J1/J2/J3 | ~$1 ea (Amazon) | Echo lines go through on-board 1k/2k dividers |
| Raspberry Pi 5 (4GB) | — | 1 | J5 + J6 | on hand | 5V from rail; UART for commands. On hand with active cooler. ⚠️ Pi 5 draws up to 4.5A — D24V50F5 at 5A is near capacity under full inference load. |
| Pi Camera Module 3 | 12MP autofocus, CSI | 1 | Pi CSI port | on hand | On hand, confirmed working. Not on this PCB — connects to Pi CSI ribbon. |
| USB speaker | Small amplified | 1 | Pi USB | ~$8 (Amazon) | Audio is Pi-side only. See vision README for playback code. |
| 2S LiPo 2200mAh | 7.4V nominal, XT30 plug | 1 | J7 (XT30) | ~$14 (Amazon) | **2S only — NOT 4S.** Soft-pack preferred for weight. |
| JGA25-370 motors | 6V, 200RPM, 4mm D-shaft | 4 | J9/J10/J11/J12 | ~$8 ea (AliExpress) | 2 per TB6612FNG. Confirm 4mm D-shaft (not N20 3mm). |
| Encoders | One per side | 2 | J13/J14 | included with motors | GPIO34 (left), GPIO35 (right). |

---

## Passives

| Ref | Value | Footprint | Qty | Purpose |
|---|---|---|---|---|
| C1,C2,C3,C18,C20,C21,C25,C26,C28,C31 | 100nF | C_0603_1608Metric | 10 | Decoupling / HF bypass |
| C17,C19,C23,C32 | 10µF | C_0805_2012Metric | 4 | Bulk ceramic decoupling |
| C30 | 1µF | C_0603_1608Metric | 1 | ESP32 EN pin delay cap |
| C24 | 100µF 16V electrolytic | CP_Radial_D6.3mm_P2.50mm | 1 | VBAT input bulk |
| C27,C29 | 470µF 16V electrolytic (low ESR) | CP_Radial_D10.0mm_P5.00mm | 2 | TB6612FNG VM bulk (one per chip, within 3mm) |
| C22 | 1000µF 16V electrolytic (low ESR) | CP_Radial_D12.5mm_P5.00mm | 1 | D24V50F5 5V output bulk (Pi inrush) |
| R1,R3,R8 | 1kΩ | R_0603_1608Metric | 3 | HC-SR04 echo divider — series |
| R2,R7,R9 | 2kΩ | R_0603_1608Metric | 3 | HC-SR04 echo divider — to GND |
| R4,R5,R10,R12 | 10kΩ | R_0603_1608Metric | 4 | Gate resistor (Q2), EN pull-up, GPIO0 pull-up, VBAT sense |
| R6 | 3.3kΩ | R_0603_1608Metric | 1 | Battery sense divider — GND side |
| R11 | 100Ω | R_0603_1608Metric | 1 | Status LED current limit |
| R13,R14 | 4.7kΩ | R_0603_1608Metric | 2 | I2C SDA/SCL pull-ups (shared by IMU + both OLEDs) |

---

## Protection & Switches

| Ref | Part | Value | Footprint | Qty | Notes |
|---|---|---|---|---|---|
| F2 | Polyfuse PPTC | 7A hold | CP_Radial_D10.0mm_P5.00mm | 1 | Littelfuse RGEF700. **7A not 5A** — avoids pre-trip sag |
| SW1 | Tactile switch | — | SW_PUSH_6mm (THT) | 1 | RESET — EN → GND |
| SW2 | Tactile switch | — | SW_PUSH_6mm (THT) | 1 | BOOT — GPIO0 → GND |
| TP1–TP6 | Test point | — | TestPoint_Pad_D1.5mm | 6 | VBAT, +5V, +3V3, GND×2, ESP_TX, ESP_RX |

---

## Connectors

| Ref | Value | Footprint | Qty | Connects |
|---|---|---|---|---|
| J7 | XT30 battery | AMASS_XT30PW-F Horizontal | 1 | Battery +/− input |
| J8 | D24V50F5 module | PinHeader_1x05_P2.54mm | 1 | Buck regulator (VIN, GND, VOUT, EN, PG) |
| J1,J2,J3 | HC-SR04 center/left/right | PinHeader_1x04_P2.54mm | 3 | Ultrasonic sensors |
| J4 | J_MAST | PinHeader_1x04_P2.54mm | 1 | I2C mast: +3V3, GND, SDA, SCL |
| J5 | J_PI_PWR | PinHeader_1x02_P2.54mm | 1 | +5V + GND to Pi |
| J6 | J_UART | PinHeader_1x03_P2.54mm | 1 | ESP_TX, ESP_RX, GND to Pi |
| J9,J10 | J_ML_F, J_MR_F | PinHeader_1x02_P2.54mm | 2 | Front motor outputs (U6) |
| J11,J12 | J_ML_R, J_MR_R | PinHeader_1x02_P2.54mm | 2 | Rear motor outputs (U7) |
| J13,J14 | ENC_L, ENC_R | PinHeader_1x03_P2.54mm | 2 | Encoders: +3V3, GND, signal |

---

## Power Rails Summary

| Rail | Source | Feeds |
|---|---|---|
| VBAT (6.4–8.4V) | J7 → F2 → Q2 | TB6612FNG VM, D24V50F5 input, battery-sense divider |
| +5V (5.0V, 5A) | D24V50F5 (J8) | Raspberry Pi, AMS1117 input, HC-SR04 VCC |
| +3V3 (3.3V, 800mA) | AMS1117 (U5) | ESP32, MPU-6050, TB6612FNG VCC/STBY, OLEDs, pull-ups, LED |

**Locked decisions:** AMS1117 fed from +5V not VBAT (thermal); 7A polyfuse; one motor per H-bridge channel; OLEDs on existing I2C bus; audio off-board on Pi.

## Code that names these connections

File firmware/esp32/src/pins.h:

#pragma once

// ── Motor control ────────────────────────────────────────────────────────────
// U6 (front) and U7 (rear) share the same control lines.
// A-channel drives left wheels, B-channel drives right wheels.
#define PIN_PWM_L   25   // IO25  → U6/U7 PWMA
#define PIN_L_IN1   26   // IO26  → U6/U7 AIN1
#define PIN_L_IN2   27   // IO27  → U6/U7 AIN2

#define PIN_PWM_R   32   // IO32  → U6/U7 PWMB
#define PIN_R_IN1   33   // IO33  → U6/U7 BIN1
#define PIN_R_IN2   14   // IO14  → U6/U7 BIN2

// Bench-only remap: puts the 4 motor inputs on the dev board's bottom pin row
// (RX2, TX2, D18, D19) when the top row is hard to reach on a breadboard.
// Not compatible with the ultrasonic sensors (they use 18/19) — see platformio.ini.
#ifdef BENCH_BOTTOM_PINS
  #undef  PIN_L_IN1
  #undef  PIN_L_IN2
  #undef  PIN_R_IN1
  #undef  PIN_R_IN2
  #define PIN_L_IN1  16   // RX2
  #define PIN_L_IN2  17   // TX2
  #define PIN_R_IN1  18   // D18
  #define PIN_R_IN2  19   // D19
#endif

// ── Encoders ─────────────────────────────────────────────────────────────────
// GPIO34/35 are input-only; no internal pull-up/down available.
#define PIN_ENC_L   34   // IO34
#define PIN_ENC_R   35   // IO35

// ── Ultrasonic (HC-SR04) ─────────────────────────────────────────────────────
// ECHO signals are 5 V; voltage dividers (R3/R7, R1/R2, R8/R9) drop to 3.3 V.
#define PIN_TRIG_L  19   // IO19
#define PIN_ECHO_L   4   // IO4

#define PIN_TRIG_C   5   // IO5
#define PIN_ECHO_C  18   // IO18

#define PIN_TRIG_R  13   // IO13
#define PIN_ECHO_R  23   // IO23

// ── I²C (MPU-6050 @ 0x68, OLEDs via J_MAST) ─────────────────────────────────
#define PIN_SDA     21   // IO21
#define PIN_SCL     22   // IO22

// ── UART to Raspberry Pi (J6) ─────────────────────────────────────────────────
#define PIN_ESP_TX  17   // IO17  → Pi RX
#define PIN_ESP_RX  16   // IO16  → Pi TX

// ── Analog ───────────────────────────────────────────────────────────────────
// Divider: R5=10 kΩ from VBAT, R6=3.3 kΩ to GND
// Vsense = Vbat × 3.3/13.3  →  Vbat = Vsense × 13.3/3.3
#define PIN_VBAT    36   // SENSOR_VP / ADC1_CH0
#define VBAT_RATIO  (13.3f / 3.3f)
#define ADC_BITS    12
#define ADC_FULL    4095.0f
#define ADC_VREF    3.3f

// ── Misc ──────────────────────────────────────────────────────────────────────
#define PIN_LED      2   // IO2  – status LED via R11 (100 Ω)
#define PIN_BOOT     0   // IO0  – BOOT/SW2, pulled high via R12 (10 kΩ)

// ── LEDC PWM ──────────────────────────────────────────────────────────────────
#define PWM_CH_L     0
#define PWM_CH_R     1
#define PWM_FREQ     20000   // 20 kHz – inaudible
#define PWM_BITS     8       // duty 0–255
